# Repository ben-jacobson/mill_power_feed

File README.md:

# mill_power_feed
Motor control code for milling machine power feed unit. Uses Platform IO with the Arduino library

Requirements:
- Use Platform IO under visual studio code
- If PIO doesn't pick this up from the .ini file, set this up as an Arudino project with the ATMega328P as the target
- If PIO doesn't pick this up from the .ini file, install the library - AccelStepper
- Compile and build in Platform IO

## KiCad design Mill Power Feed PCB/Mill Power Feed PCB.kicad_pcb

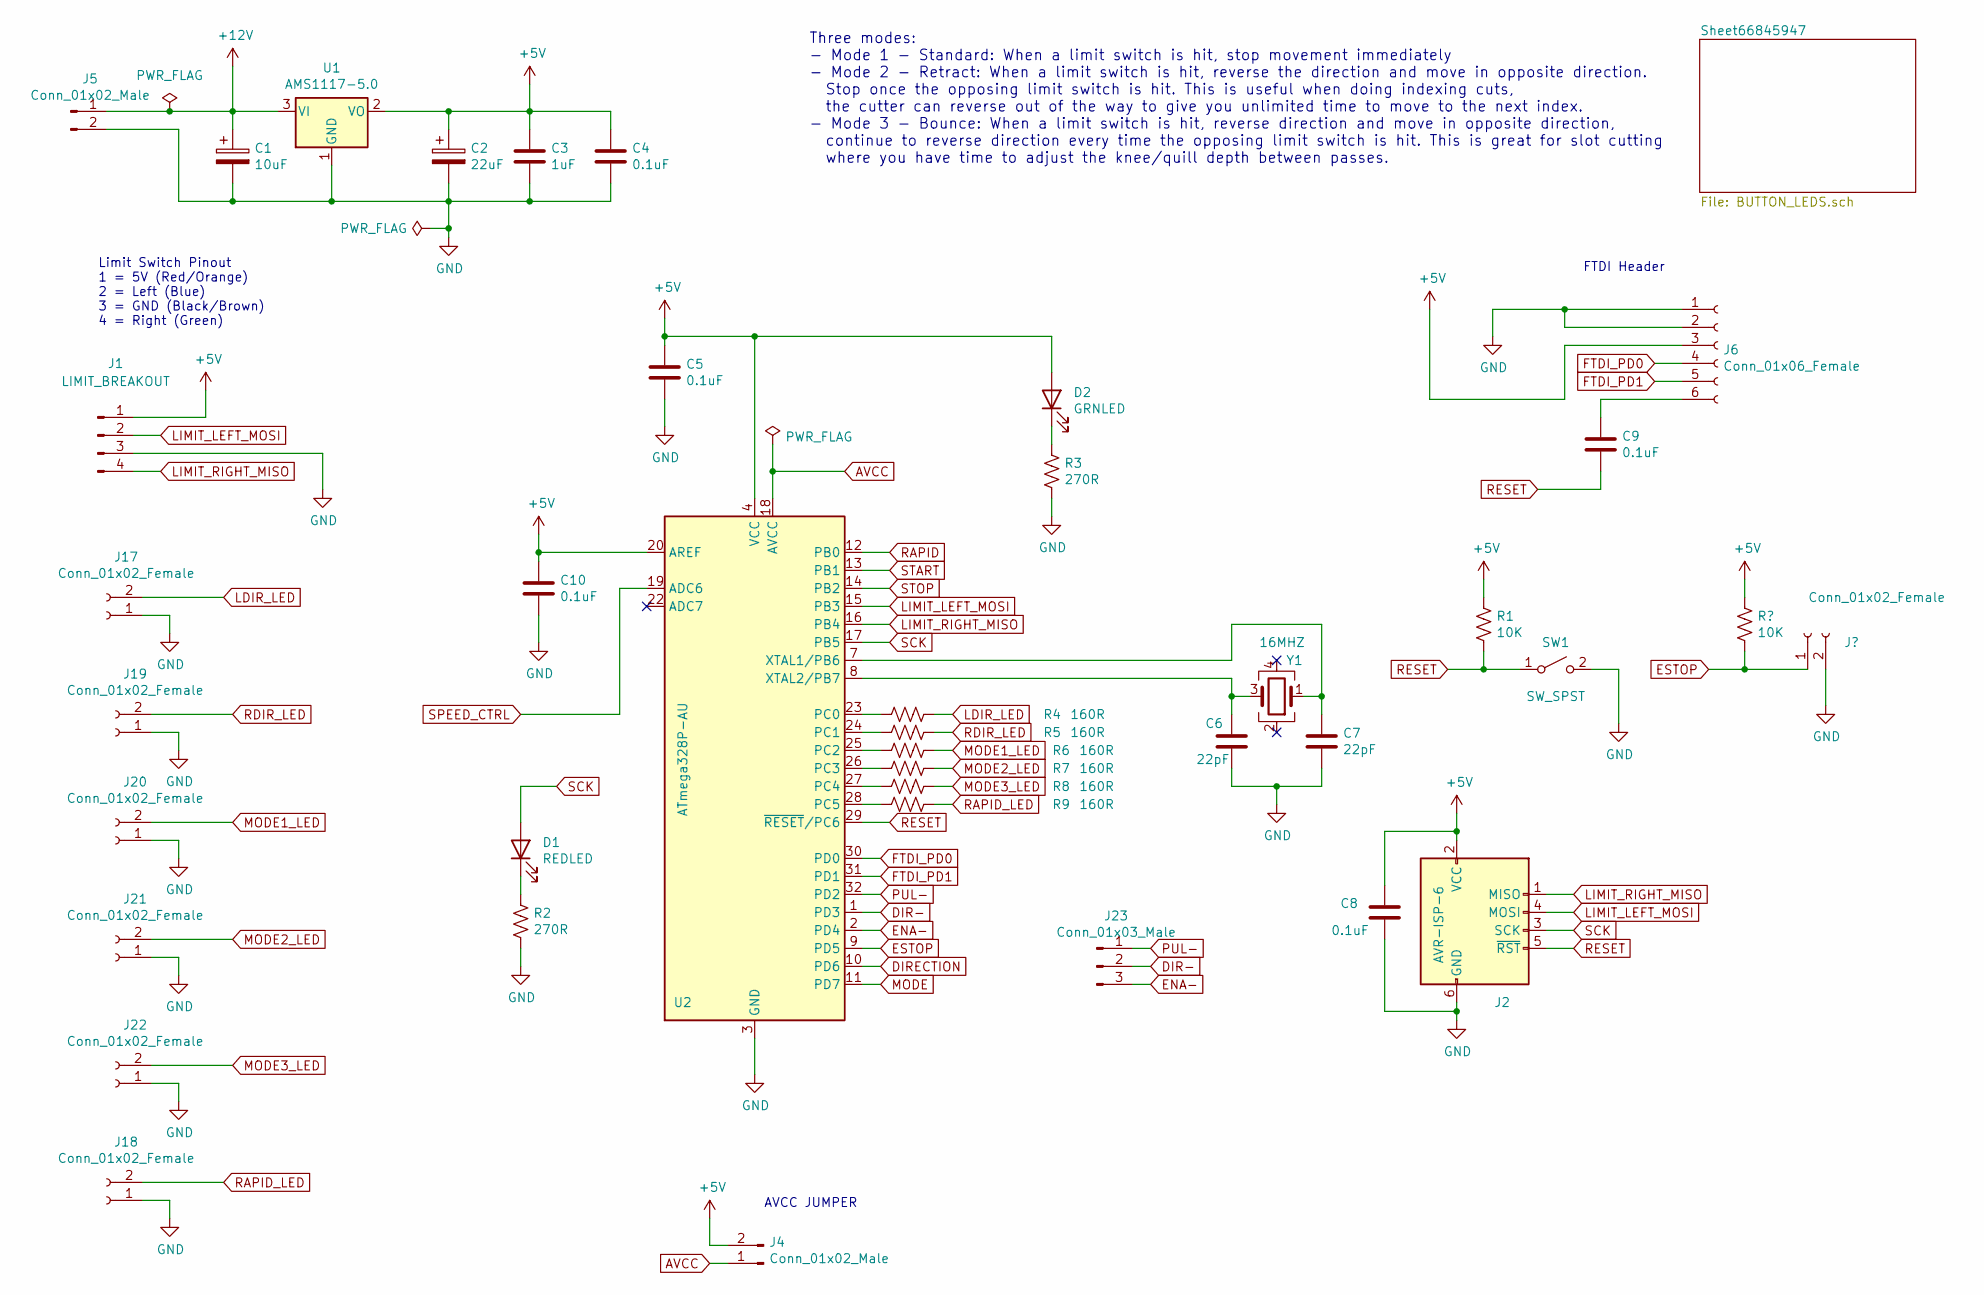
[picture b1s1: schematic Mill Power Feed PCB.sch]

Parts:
C1: 10uF; C_Elec_4x5.4; LCSC C134721
C2: 22uF; CP_EIA-3528-21_Kemet-B; LCSC C8020
C3: 1uF; C_0603_1608Metric; LCSC C28323
C4, C5, C8, C9, C10: 0.1uF; C_0603_1608Metric; LCSC C14663
C6, C7: 22pF; C_0603_1608Metric; LCSC C388039
D1: REDLED; LED_0603_1608Metric; LCSC C2286
D2: GRNLED; LED_0603_1608Metric; LCSC C72043
J1: LIMIT_BREAKOUT; JST_XH_B4B-XH-AM_1x04_P2.50mm_Vertical
J2: AVR-ISP-6; PinHeader_2x03_P2.54mm_Vertical
J4: Conn_01x02_Male; PinHeader_1x02_P2.54mm_Vertical
J5: Conn_01x02_Male; PinHeader_1x02_P2.54mm_Horizontal
J6: Conn_01x06_Female; PinSocket_1x06_P2.54mm_Vertical
J17, J18, J19, J20, J21, J22: Conn_01x02_Female; JST_XH_B2B-XH-AM_1x02_P2.50mm_Vertical
J23: Conn_01x03_Male; JST_XH_B3B-XH-AM_1x03_P2.50mm_Vertical
R1: 10K; R_0603_1608Metric; LCSC C25804
R2, R3: 270R; R_0603_1608Metric; LCSC C22966
R4, R5, R6, R7, R8, R9: 160R; R_0603_1608Metric
SW1: SW_SPST; SW_Push_1P1T_NO_6x6mm_H9.5mm; LCSC C620316
U1: AMS1117-5.0; SOT-223-3_TabPin2; LCSC C6187
U2: ATmega328P-AU; TQFP-32_7x7mm_P0.8mm; LCSC C14877
Y1: 16MHZ; Crystal_SMD_3225-4Pin_3.2x2.5mm; LCSC C13738

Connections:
+5V: C2.1, C3.1, C4.1, C5.1, C8.1, C10.1, D2.2 (A), J1.1, J2.2 (VCC), J4.2, J6.3, R1.1, U1.2 (VO), U2.4 (VCC), U2.6 (VCC), U2.20 (AREF); also elsewhere on the board
DIR-: J23.2, U2.1 (PD3)
DIRECTION: U2.10 (PD6); also elsewhere on the board
ENA-: J23.3, U2.2 (PD4)
FTDI_PD0: J6.4, U2.30 (PD0)
FTDI_PD1: J6.5, U2.31 (PD1)
GND: C1.2, C2.2, C3.2, C4.2, C5.2, C6.2, C7.2, C8.2, C10.2, J1.3, J2.6 (GND), J5.2, J6.1, J6.2, J17.1, J18.1, J19.1, J20.1, J21.1, J22.1, R2.2, R3.2, SW1.2 (B), U1.1 (GND), U2.3 (GND), U2.5 (GND), U2.21 (GND); also elsewhere on the board
LDIR_LED: J17.2, R4.1
LIMIT_LEFT_MOSI: J1.2, J2.4 (MOSI), U2.15 (PB3)
LIMIT_RIGHT_MISO: J1.4, J2.1 (MISO), U2.16 (PB4)
MODE: U2.11 (PD7); also elsewhere on the board
MODE1_LED: J20.2, R6.1
MODE2_LED: J21.2, R7.1
MODE3_LED: J22.2, R8.1
unnamed: C6.1, U2.8 (XTAL2/PB7), Y1.3
unnamed: C7.1, U2.7 (XTAL1/PB6), Y1.1
unnamed: C9.1, J6.6
unnamed: D1.1 (K), R2.1
unnamed: D2.1 (K), R3.1
unnamed: R4.2, U2.23 (PC0)
unnamed: R5.2, U2.24 (PC1)
unnamed: R6.2, U2.25 (PC2)
unnamed: R7.2, U2.26 (PC3)
unnamed: R8.2, U2.27 (PC4)
unnamed: R9.2, U2.28 (PC5)
PUL-: J23.1, U2.32 (PD2)
RAPID: U2.12 (PB0); also elsewhere on the board
RAPID_LED: J18.2, R9.1
RDIR_LED: J19.2, R5.1
RESET: C9.2, J2.5 (~RST), R1.2, SW1.1 (A), U2.29 (~RESET~/PC6)
SCK: D1.2 (A), J2.3 (SCK), U2.17 (PB5)
SPEED_CTRL: U2.19 (ADC6); also elsewhere on the board
START: U2.13 (PB1); also elsewhere on the board
STOP: U2.14 (PB2); also elsewhere on the board

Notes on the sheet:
AVCC JUMPER
FTDI Header
Three modes: - Mode 1 - Standard: When a limit switch is hit, stop movement immediately - Mode 2 - Retract: When a limit switch is hit, reverse the direction and move in opposite direction. Stop once the opposing limit switch is hit. This is useful when doing indexing cuts, the cutter can reverse o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
Limit Switch Pinout 1 = 5V (Red/Orange) 2 = Left (Blue) 3 = GND (Black/Brown) 4 = Right (Green)

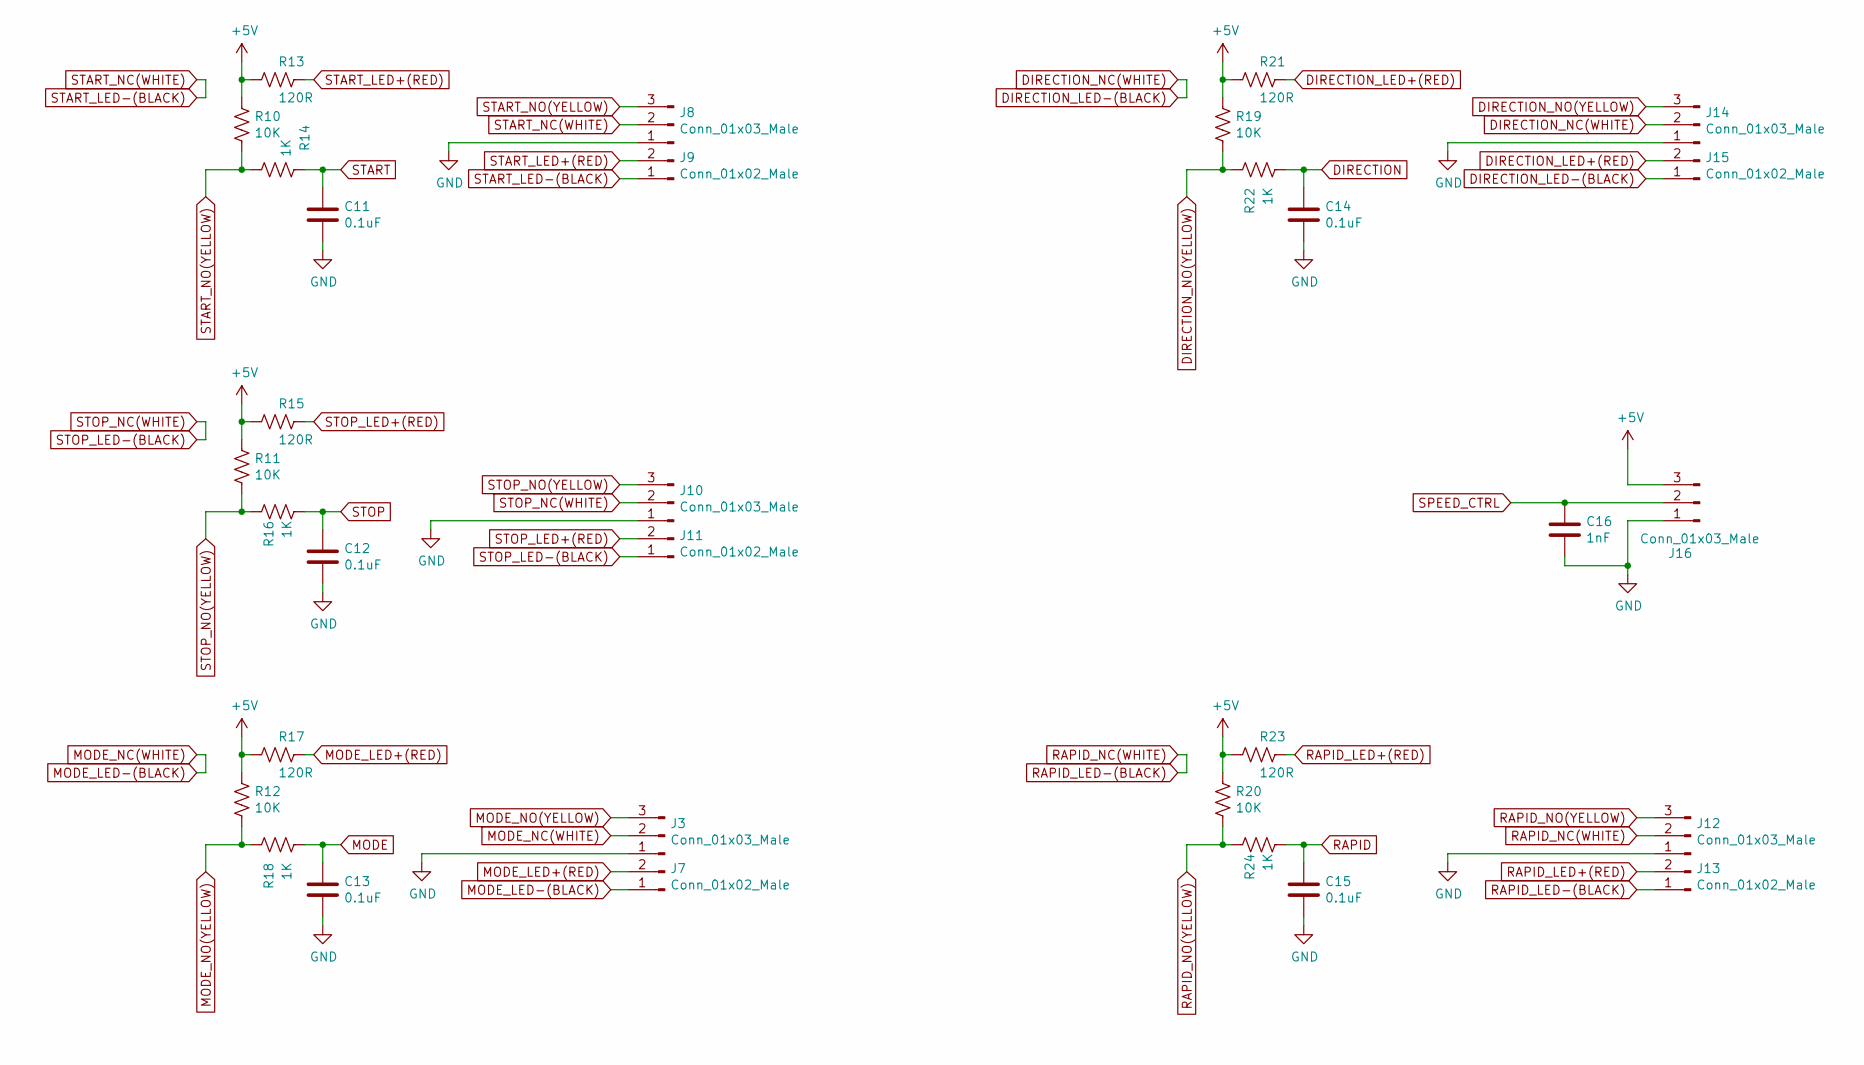
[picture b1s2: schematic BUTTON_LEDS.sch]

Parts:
C11, C12, C13, C14, C15: 0.1uF; C_0603_1608Metric
C16: 1nF; C_0603_1608Metric
J3, J8, J10, J12, J14, J16: Conn_01x03_Male; JST_XH_B3B-XH-AM_1x03_P2.50mm_Vertical
J7, J9, J11, J13, J15: Conn_01x02_Male; JST_XH_B2B-XH-AM_1x02_P2.50mm_Vertical
R10, R11, R12, R19, R20: 10K; R_0603_1608Metric
R13, R15, R17, R21, R23: 120R; R_0603_1608Metric
R14, R16, R18, R22, R24: 1K; R_0603_1608Metric

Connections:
+5V: J16.3, R10.1, R11.1, R12.1, R13.2, R15.2, R17.2, R19.1, R20.1, R21.2, R23.2; also elsewhere on the board
DIRECTION: C14.1, R22.2; also elsewhere on the board
DIRECTION_LED+(RED): J15.2, R21.1
DIRECTION_LED-(BLACK): J14.2, J15.1
DIRECTION_NO(YELLOW): J14.3, R19.2, R22.1
GND: C11.2, C12.2, C13.2, C14.2, C15.2, C16.2, J3.1, J8.1, J10.1, J12.1, J14.1, J16.1; also elsewhere on the board
MODE: C13.1, R18.2; also elsewhere on the board
MODE_LED+(RED): J7.2, R17.1
MODE_LED-(BLACK): J3.2, J7.1
MODE_NO(YELLOW): J3.3, R12.2, R18.1
RAPID: C15.1, R24.2; also elsewhere on the board
RAPID_LED+(RED): J13.2, R23.1
RAPID_LED-(BLACK): J12.2, J13.1
RAPID_NO(YELLOW): J12.3, R20.2, R24.1
SPEED_CTRL: C16.1, J16.2; also elsewhere on the board
START: C11.1, R14.2; also elsewhere on the board
START_LED+(RED): J9.2, R13.1
START_LED-(BLACK): J8.2, J9.1
START_NO(YELLOW): J8.3, R10.2, R14.1
STOP: C12.1, R16.2; also elsewhere on the board
STOP_LED+(RED): J11.2, R15.1
STOP_LED-(BLACK): J10.2, J11.1
STOP_NO(YELLOW): J10.3, R11.2, R16.1

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
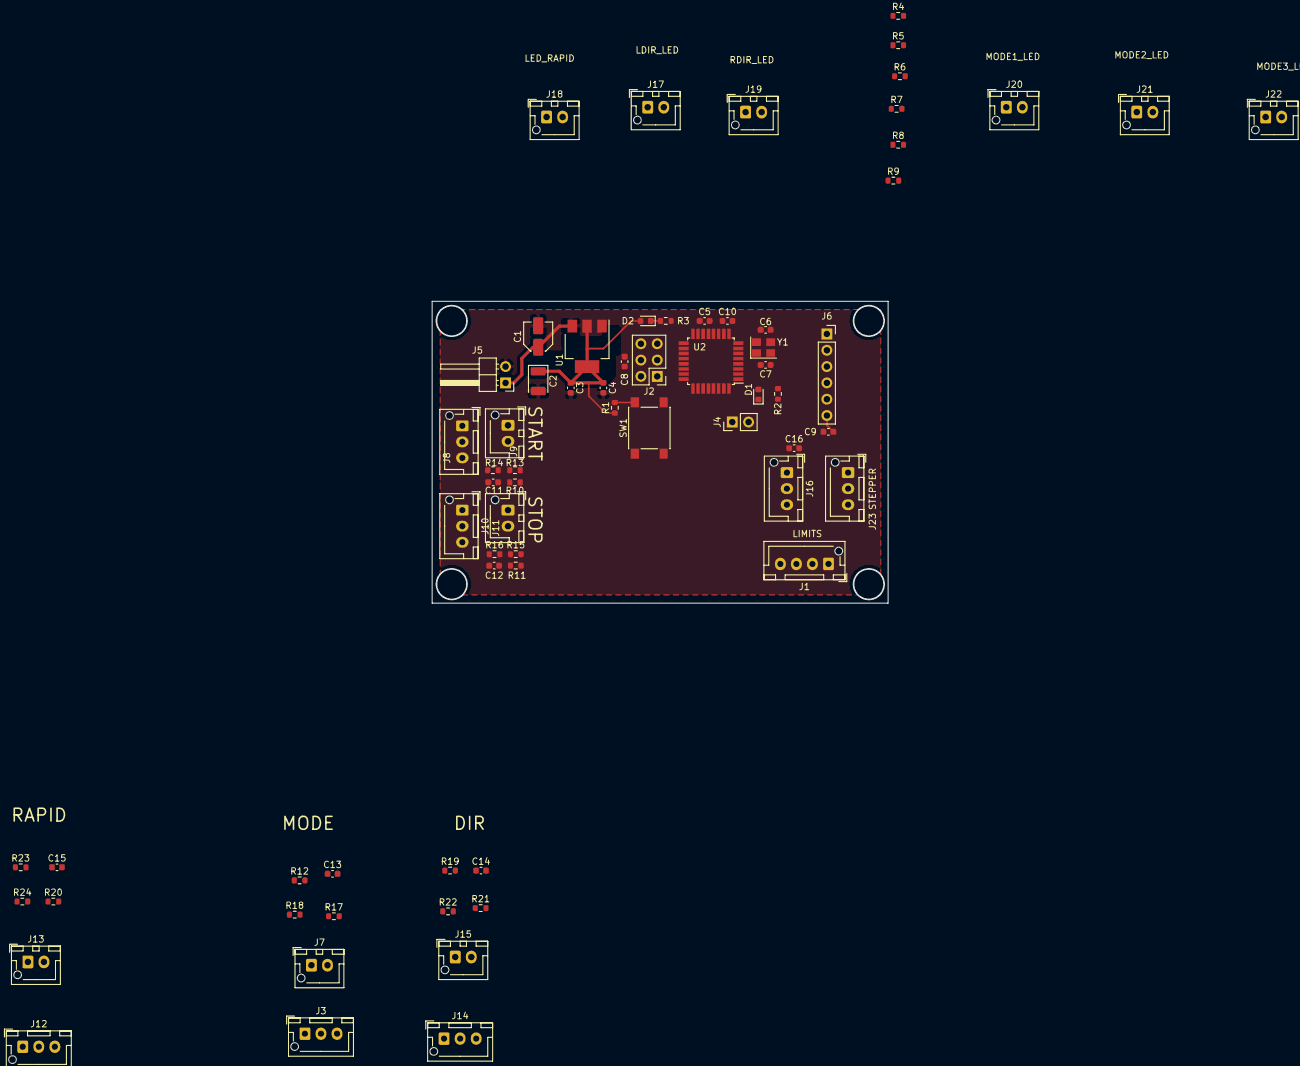
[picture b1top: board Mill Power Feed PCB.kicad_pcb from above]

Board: 2 copper layers, 71.0 x 47.0 mm, 69 parts (0 on the bottom side), 51 nets.

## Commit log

2024-10-06 Tidied up stop code, added an extra pin for eStop and attached an interrupt, will enable it when we add in hardware
2024-10-06 code tidy up re acceleration, yet to be tested in hardware
2024-10-06 Tweaked acceleration to the kinematics of the machine, however am having trouble now the stop function within the library seems to ignore deceleration, may need to refactor and use a new library...
2024-10-06 fixed issue where motor stopping would stop without decelleration, also put in new safety feature to prevent rapiding into limit switches.
2024-10-06 Added kicad schematics
    Board layout is incomplete. Decision was made to switch from JST crimp connectors to phoenix connectors which hasn't happened yet.
